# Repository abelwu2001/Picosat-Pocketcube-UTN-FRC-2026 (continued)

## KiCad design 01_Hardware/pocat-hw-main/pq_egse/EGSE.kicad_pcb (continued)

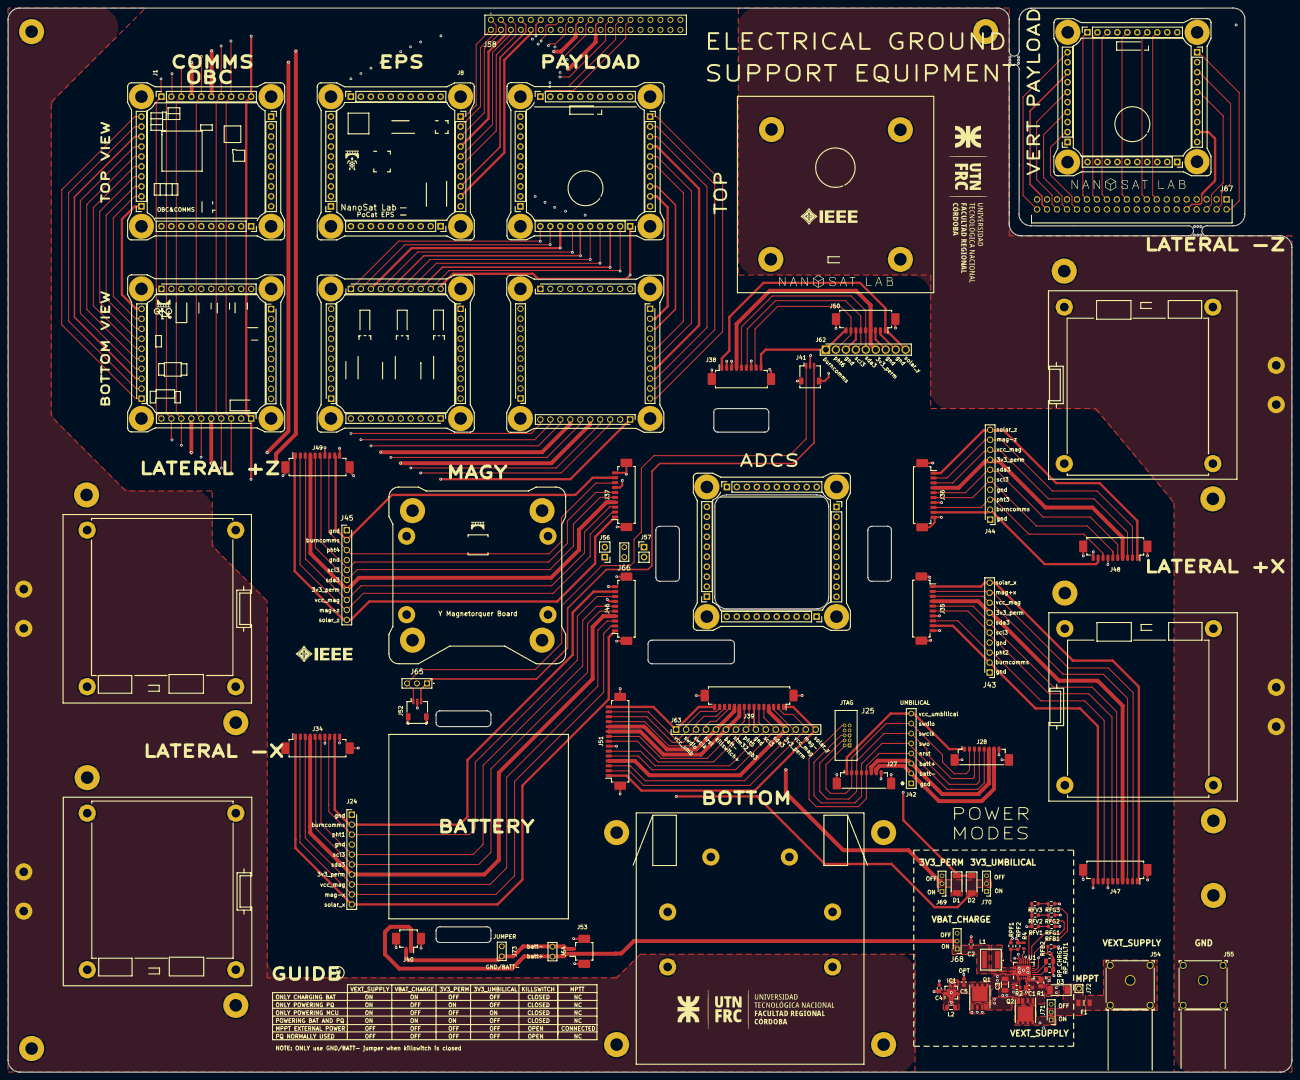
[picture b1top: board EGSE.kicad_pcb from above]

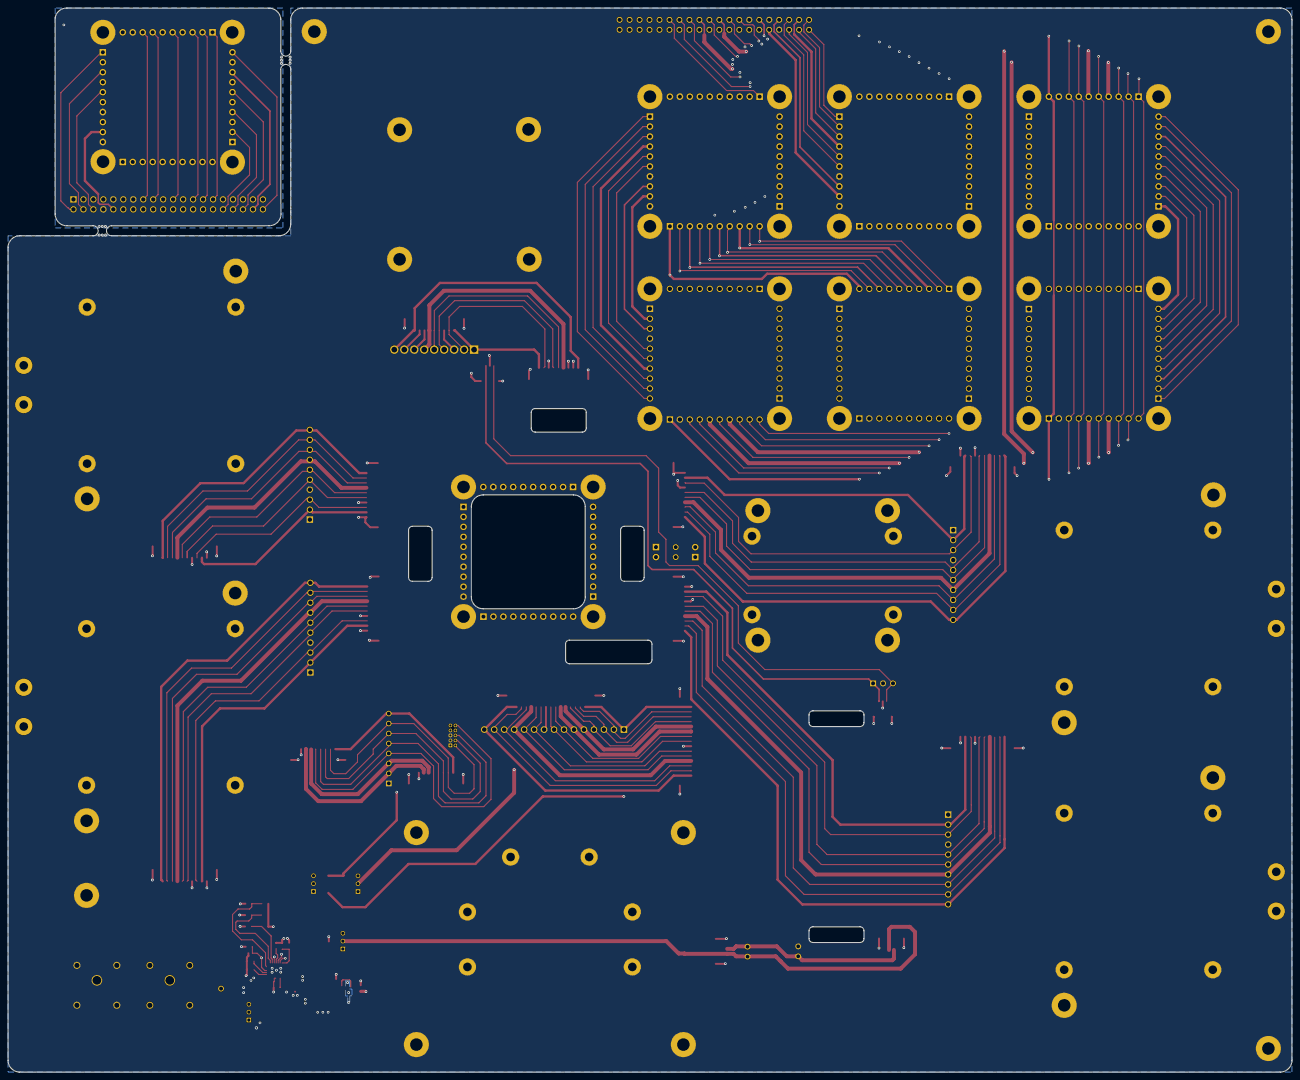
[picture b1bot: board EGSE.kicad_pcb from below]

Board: 6 copper layers, 327.0 x 271.0 mm, 195 parts (2 on the bottom side), 74 nets.

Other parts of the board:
Annotation1#2: Silkscreen_Annotation; IEEE_logo__Annotation1
Annotation1#3, Annotation1#4: Silkscreen_Annotation; Bridgemaker__Annotation1
Annotation2#2: Silkscreen_Annotation; IEEE_logo__Annotation2
Annotation3#2: Silkscreen_Annotation; NSL_long__Annotation3
mouse-bite-2.54mm-slot, mouse-bite-2.54mm-slot#2: VAL**; mouse-bite-2.54mm-slot__mouse-bite-2.54mm-slot

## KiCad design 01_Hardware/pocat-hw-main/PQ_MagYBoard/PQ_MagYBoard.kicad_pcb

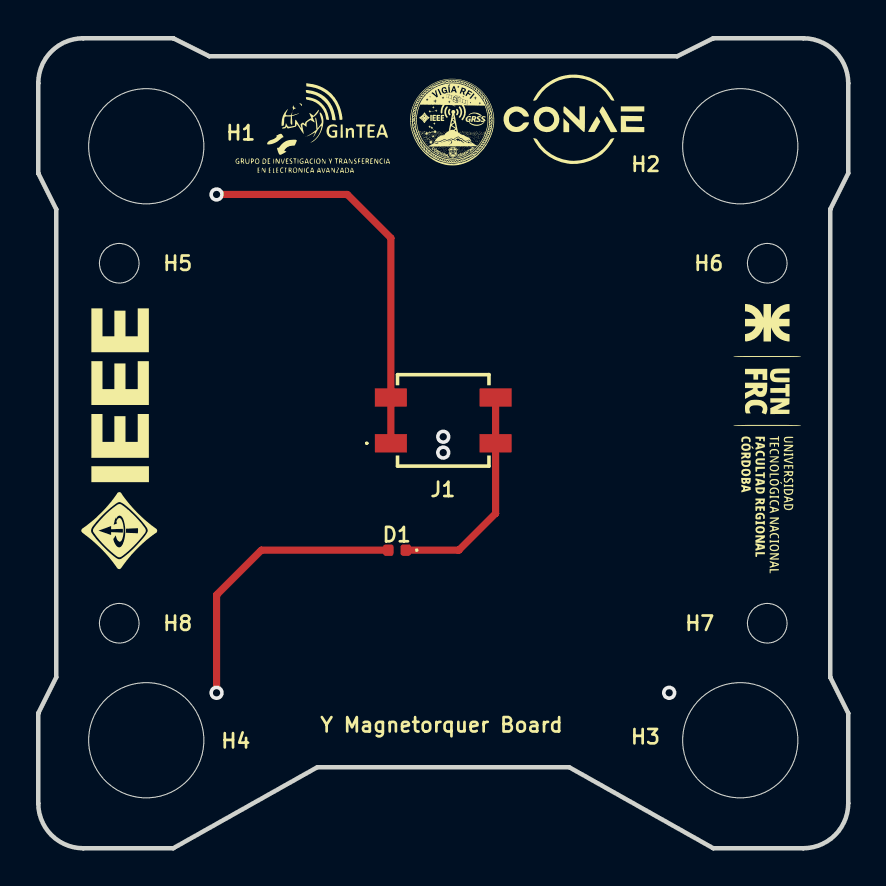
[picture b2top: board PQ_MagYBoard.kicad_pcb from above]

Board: 6 copper layers, 45.0 x 45.0 mm, 11 parts (0 on the bottom side), 2 nets.

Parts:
Annotation1: Silkscreen_Annotation; IEEE_logo__Annotation1
D1: LED; D1__96abf5d7
H1: MountingHole; H1__4e36dd2d
H2: MountingHole; H2__04eba765
H3: MountingHole; H3__b5fb1087
H4: MountingHole; H4__a7a81e5c
H5: MountingHole; H5__5195467b
H6: MountingHole; H6__80f6b20b
H7: MountingHole; H7__513e248b
H8: MountingHole; H8__01ccc00b
J1: M20-7810245; J1__1c8c80f3

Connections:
/MAG+Y: D1.1 (K), J1.2, J1.4
/VCC_MAG: D1.2 (A), J1.1, J1.3

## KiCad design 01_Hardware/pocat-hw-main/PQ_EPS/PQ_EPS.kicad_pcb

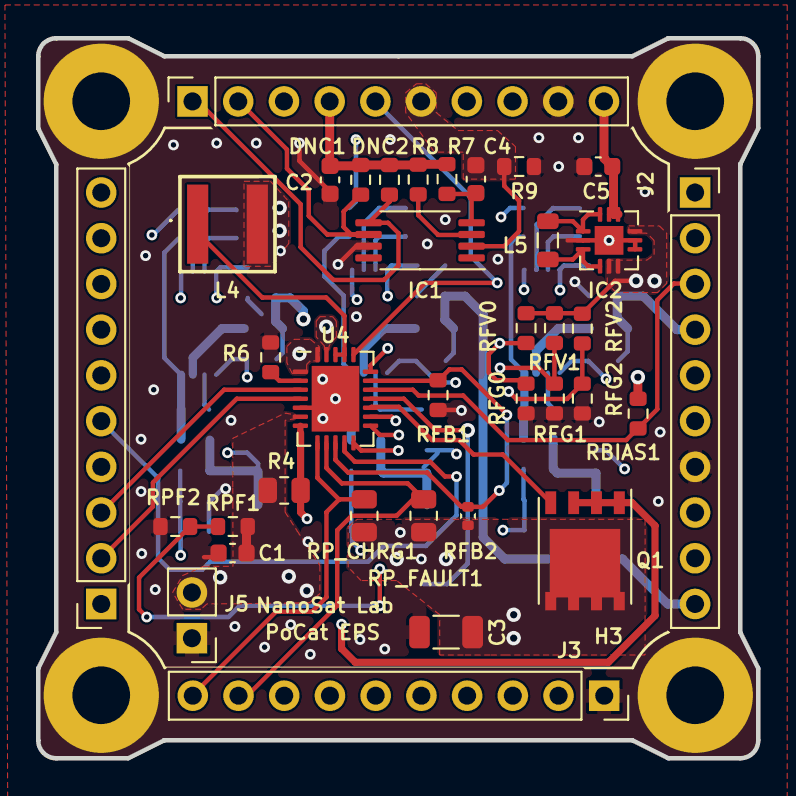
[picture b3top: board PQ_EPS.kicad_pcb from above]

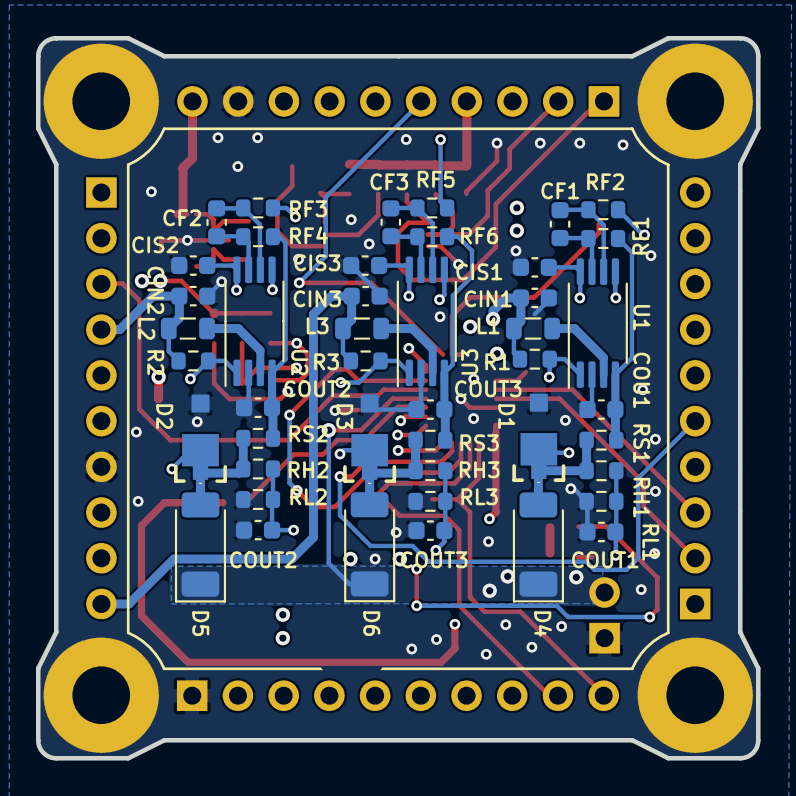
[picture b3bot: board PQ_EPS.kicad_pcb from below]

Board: 4 copper layers, 40.0 x 40.0 mm, 85 parts (45 on the bottom side), 52 nets.

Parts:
C1: 2.2u; C1__85906104
C2: 10u; C2__3bb3261a
C3: 100u; C3__1b16b82f
C4: 0.1u; C4__8813a4fd
C5: 22u; C5__10c63672
CF1: 1u; CF1__1f269640
CF2: 1u; CF2__bf330c01
CF3: 1u; CF3__dc4340d5
CIN1: 1.5u; CIN1__4d5a425d
CIN2: 1.5u; CIN2__61dff1fe
CIN3: 1.5u; CIN3__7a7f343d
CIS1: 1n; CINSNS1__fe801517
CIS2: 1n; CINSNS2__c8bb742b
CIS3: 1n; CINSNS3__0692e306
COU1: 10u; COUT1__ab158bdd
COUT1: 1n; COUTSNS1__a3c0c3c5
COUT2: 10u; COUT2__652cde38
COUT2#2: 1n; COUTSNS2__7fceb7d9
COUT3: 10u; COUT3__754a9436
COUT3#2: 1n; COUTSNS3__d7212c9c
D1: SMM4F; D1__d6a92ff9
D2: SMM4F; D2__ff0ca32b
D3: SMM4F; D3__e18f0f22
D4: shottky; D4__8296a06b
D5: shottky; D5__9ba6cb21
D6: shottky; D6__c3fa03f0
DNC1: 20k; DNC1__f835551e
DNC2: 20k; DNC2__33baa008
H1: MountingHole_Pad; H1__55b0f0f4
H2: MountingHole_Pad; H2__8e44a857
H3: MountingHole_Pad; H3__b7d146b7
H4: MountingHole_Pad; H4__41eeead0
IC1: DS2782E+; IC1__4bc49ce2
IC2: ISL9120IRTNZ; IC2__20e1d699
J1: CES-110-02-L-S; J1__41ef131c
J2: CES-110-02-L-S; J2__a6eda72d
J3: CES-110-02-L-S; J3__f3199705
J4: CES-110-02-L-S; J4__cbe1d312
J5: J5__02e0e550
L1: 10u; L1__28ad8ce4
L2: 10u; L2__ba5a3009
L3: 10u; L3__2d21b16b
L4: 2.2u; L4__0e1a387a
L5: 1u; L5__3c55d55a
Q1: SIR424DP; Q1__7e14e801
R1: 1k; R1__714a8ecb
R2: 1k; R2__9665c163
R3: 1k; R3__0ad47374
R4: 75m; R4__23007612
R6: 2k; R6__9883130c
R7: 510; R7__5afebccb
R8: 1k; R8__c5a4b0be
R9: 15m; R9__b30fbfff
RBIAS1: 10k; RBIAS1__42875ef3
RF1: 1k; RF1__b4a62e9b
RF2: 1k; RF2__79efa971
RF3: 1k; RF3__bcc6cc11
RF4: 1k; RF4__cdcae543
RF5: 1k; RF5__f4b268ee
RF6: 1k; RF6__ccc287bf
RFB1: 68k; RFB1__c3f0ad02
RFB2: 255k; RFB2__4535851b
RFG0: 1k; RFG0__3a5b81d0
RFG1: 1k; RFG1__e70eb10d
RFG2: 1k; RFG2__d57aa5a1
RFV0: 1k; RFV0__0fa13d2d
RFV1: 1k; RFV1__fbfc8f7b
RFV2: 1k; RFV2__f2fc9b41
RH1: 910k; RH1__fc164062
RH2: 910k; RH2__583a5c2e
RH3: 910k; RH3__ecdadcf0
RL1: 360k; RL1__fa346202
RL2: 360k; RL2__b23261de
RL3: 360k; RL3__61c11c4e
RPF1: 147k; RPF1__76985f45
RPF2: 68k; RPF2__25740c8e
RP_CHRG1: 5k; RP_CHRG1__a22c6ae2
RP_FAULT1: 5k; RP_FAULT1__5c0411cb
RS1: 300m; RS1__0808f33b
RS2: 300m; RS2__556b6153
RS3: 300m; RS3__b8c6c485
U1: SPV1040TTR; U1__eb7258e8
U2: SPV1040TTR; U2__41f13721
U3: SPV1040TTR; U3__48f96149
U4: LTC4040IUFD#PBF; U4__55343438

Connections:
3V3_PERM: C5.2, IC2.10 (FB), IC2.11 (VOUT), J1.10, RBIAS1.2
BATT-: C4.2, IC1.2 (VSS), J1.6, R9.1
BATT_NTC: J2.3, RBIAS1.1, U4.17 (NTC)
CHOUT: C3.1, IC2.5 (VIN_1), IC2.6 (VIN_2), IC2.9 (EN), Q1.5 (D), RFB2.2, RFV0.1, RFV1.1, RFV2.1, RP_CHRG1.1, RP_FAULT1.1, U4.1 (VSYS), U4.24 (VSYS)
CHRG: J3.10, RP_CHRG1.2, U4.8 (CHRG#)
CHRGOFF: J4.2, U4.4 (CHGOFF)
CLPROG: J4.3, U4.3 (CLPROG)
F0: RFG0.1, RFV0.2, U4.14 (F0)
F1: RFG1.1, RFV1.2, U4.13 (F1)
F2: RFG2.1, RFV2.2, U4.12 (F2)
FAULT: J3.9, RP_FAULT1.2, U4.9 (FAULT#)
GND: C1.2, C2.2, C3.2, C5.1, CIN1.1, CIN2.1, CIN3.1, CIS1.1, CIS2.1, CIS3.1, COU1.1, COUT1.1, COUT2.1, COUT2#2.1, COUT3.1, COUT3#2.1, D1.2, D2.2, D3.2, H1.1, H2.1, H3.1, H4.1, IC1.7 (SNS), IC2.2 (PGND), IC2.7 (BYPS), IC2.8 (GND), IC2.13 (EP), J1.9, J2.7, J3.1, J5.1, R6.1, R9.2, RFB1.2, RFG0.2, RFG1.2, RFG2.2, RL1.2, RL2.2, RL3.2, RPF2.1, U1.2 (GND), U2.2 (GND), U3.2 (GND), U4.5 (BSTOFF), U4.25 (EPAD)
KILLSWITCH+: C2.1, DNC1.2, DNC2.2, J1.4, L4.2, R7.2, R8.2, U4.23 (BAT)
NRST: J4.5, U4.11 (RST#)
unnamed: D1.1, D4.2, RF2.2, RH1.1, RS1.2
unnamed: D2.1, D5.2, RF3.2, RH2.1, RS2.2
unnamed: D3.1, D6.2, RF5.2, RH3.1, RS3.2
unnamed: C4.1, IC1.4 (VDD), R7.1
unnamed: IC1.3 (VIN), R8.1
unnamed: IC2.3 (LX1_1), IC2.4 (LX1_2), L5.1
unnamed: IC2.1 (LX2_1), IC2.12 (LX2_2), L5.2
unnamed: L4.1, U4.21 (SW), U4.22 (SW)
unnamed: Q1.4 (G), U4.15 (IGATE)
unnamed: CF1.1, RF2.1, U1.6 (ICTRL-MINUS)
unnamed: CF1.2, RF1.1, U1.7 (ICTRL-PLUS)
unnamed: L1.1, U1.3 (LX)
unnamed: CIS1.2, R1.1, U1.1 (MPP-SET), U1.8 (XSHUT)
unnamed: COUT1.2, RH1.2, RL1.1, U1.5 (VCTRL)
unnamed: COU1.2, RF1.2, RS1.1, U1.4 (VOUT)
unnamed: CF2.1, RF3.1, U2.6 (ICTRL-MINUS)
unnamed: CF2.2, RF4.1, U2.7 (ICTRL-PLUS)
unnamed: L2.2, U2.3 (LX)
unnamed: CIS2.2, R2.1, U2.1 (MPP-SET), U2.8 (XSHUT)
unnamed: COUT2#2.2, RH2.2, RL2.1, U2.5 (VCTRL)
unnamed: COUT2.2, RF4.2, RS2.1, U2.4 (VOUT)
unnamed: CF3.1, RF5.1, U3.6 (ICTRL-MINUS)
unnamed: CF3.2, RF6.1, U3.7 (ICTRL-PLUS)
unnamed: L3.2, U3.3 (LX)
unnamed: CIS3.2, R3.1, U3.1 (MPP-SET), U3.8 (XSHUT)
unnamed: COUT3#2.2, RH3.2, RL3.1, U3.5 (VCTRL)
unnamed: COUT3.2, RF6.2, RS3.1, U3.4 (VOUT)
unnamed: RFB1.1, RFB2.1, U4.10 (RSTFB), U4.18 (BSTFB)
unnamed: Q1.1 (S), Q1.2 (S), Q1.3 (S), R4.2, U4.7 (CLN)
unnamed: RPF1.1, RPF2.2, U4.19 (PFI)
OVSNS: C1.1, D4.1, D5.1, D6.1, J5.2, R4.1, RPF1.2, U4.6 (VIN), U4.16 (OVSNS)
PFO: J1.5, U4.20 (PF0#)
PROG: R6.2, U4.2 (PROG)
SCL1: DNC1.1, IC1.6 (SCL), J1.2
SDA1: DNC2.1, IC1.5 (SDA), J1.1
SOLAR_X: CIN1.2, J4.1, L1.2, R1.2
SOLAR_Y: CIN2.2, J2.4, L2.1, R2.2
SOLAR_Z: CIN3.2, J2.10, L3.1, R3.2

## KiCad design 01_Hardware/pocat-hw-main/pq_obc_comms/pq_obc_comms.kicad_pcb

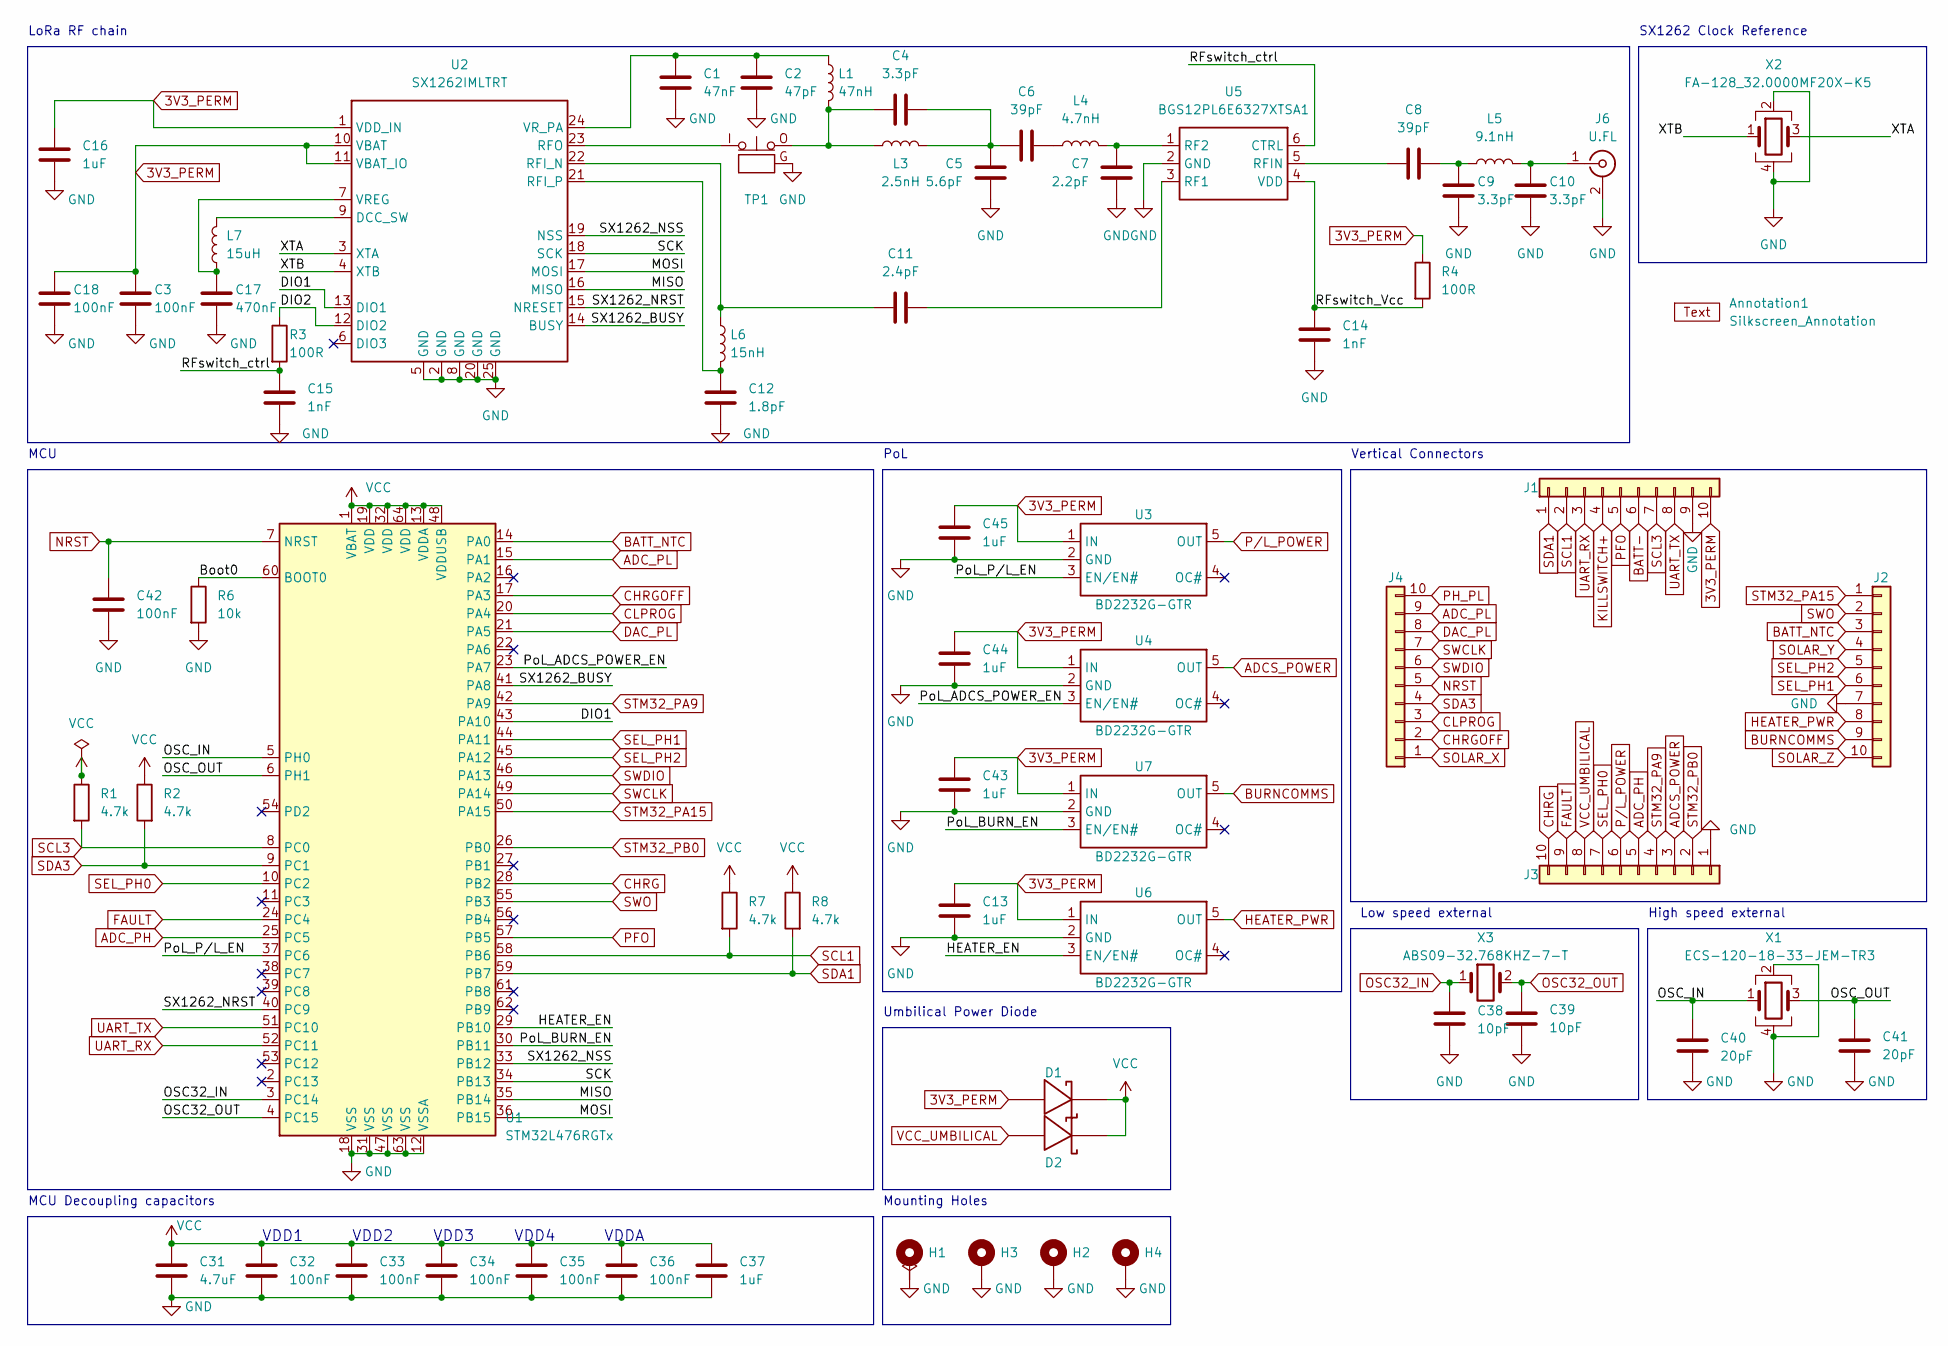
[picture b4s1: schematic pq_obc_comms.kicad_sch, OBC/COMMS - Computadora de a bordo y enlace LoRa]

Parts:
Annotation1: Silkscreen_Annotation; Annotation1__e7e7156d
C1: 47nF; C1__ca774a57; Manufacturer Part Numbe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 GRM155R71C473KA01J
C2: 47pF; C2__72c49c38; Manufacturer Part Numbe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 GJM1555C1H470JB01J
C3: 100nF; C3__bcfd69c3; Manufacturer Part Numbe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 GRM188R72A104KA35J
C4: 3.3pF; C4__90207b2c; Manufacturer Part Numbe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 600L3R3BT200T
C5: 5.6pF; C5__346fd701; Manufacturer Part Numbe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 600L5R6BTN200T
C6: 39pF; C6__2c3003df; Manufacturer Part Numbe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 GJM1555C1H390FB01D
C7: 2.2pF; C7__ead5be2a; Manufacturer Part Numbe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 600L2R2BT200T
C8: 39pF; C8__3b28bfd6; Manufacturer Part Numbe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 GJM1555C1H390FB01D
C9: 3.3pF; C9__dc49ac9c; Manufacturer Part Numbe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 600L3R3BT200T
C10: 3.3pF; C10__82ed297d; Manufacturer Part Numbe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 600L3R3BT200T
C11: 2.4pF; C11__b2db7fb1; Manufacturer Part Numbe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 600L2R4BW200T
C12: 1.8pF; C12__b2c7e8c6; Manufacturer Part Numbe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 600L1R8BW200T
C13: 1uF; C13__d1b90dea; Manufacturer Part Numbe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 GRM188R61A105KA61D
C14: 1nF; C14__c8ce7f45; Manufacturer Part Numbe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 0603B102K500CT
C15: 1nF; C15__0dffcb91; Manufacturer Part Numbe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 0603B102K500CT
C16: 1uF; C16__58b6b3e1; Manufacturer Part Numbe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 GRM188R61A105KA61D
C17: 470nF; C17__74bd322c; Manufacturer Part Numbe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 GRM188R7YA474KE05D
C18: 100nF; C18__0129d3c2; Manufacturer Part Numbe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 GRM188R72A104KA35J
C31: 4.7uF; C31__e4047c3f; Manufacturer Part Numbe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 GRT188R61E475KE13D
C32: 100nF; C32__096e5967; Manufacturer Part Numbe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 GRM188R72A104KA35J
C33: 100nF; C33__1d37b461; Manufacturer Part Numbe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 GRM188R72A104KA35J
C34: 100nF; C34__f54a60c3; Manufacturer Part Numbe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 GRM188R72A104KA35J
C35: 100nF; C35__eea0baec; Manufacturer Part Numbe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 GRM188R72A104KA35J
C36: 100nF; C36__1330f687; Manufacturer Part Numbe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 GRM188R72A104KA35J
C37: 1uF; C37__f9cb8991; Manufacturer Part Numbe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 GRM188R61A105KA61D
C38: 10pF; C38__fabc3299; Manufacturer Part Numbe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 06035A100GAT2A
C39: 10pF; C39__0234df5a; Manufacturer Part Numbe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 06035A100GAT2A
C40: 20pF; C40__9df9f696; Manufacturer Part Numbe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 GCM1885C2A200JA16D
C41: 20pF; C41__0aea1b69; Manufacturer Part Numbe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 GCM1885C2A200JA16D
C42: 100nF; C42__d2aef4f4; Manufacturer Part Numbe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 GRM188R72A104KA35J
C43: 1uF; C43__5c5681ac; Manufacturer Part Numbe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 GRM188R61A105KA61D
C44: 1uF; C44__a1850039; Manufacturer Part Numbe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 GRM188R61A105KA61D
C45: 1uF; C45__bee54487; Manufacturer Part Numbe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 GRM188R61A105KA61D
D1: RBS1LAM40ATR; D1__334df4c5; Manufacturer Part Numbe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 RBS1LAM40ATR
D2: RBS1LAM40ATR; D2__bd2b3331; Manufacturer Part Numbe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 RBS1LAM40ATR
H1: MountingHole_Pad; H1__a8eef03d
H2: MountingHole_Pad; H2__7afaf494
H3: MountingHole_Pad; H3__f70388f1
H4: MountingHole_Pad; H4__f801a1cd
J1: Conn_01x10; J1__ce21188f; Manufacturer Part Numbe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 CES-110-01-T-S
J2: Conn_01x10; J2__a63bc9cd; Manufacturer Part Numbe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 CES-110-01-T-S
J3: Conn_01x10; J3__57c77339; Manufacturer Part Numbe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 CES-110-01-T-S
J4: Conn_01x10; J4__71042816; Manufacturer Part Numbe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 CES-110-01-T-S
J6: U.FL; J6__95db4f5f; Manufacturer Part Numbe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 U.FL-R-SMT-1(10)
L1: 47nH; L1__f2e2799c; Manufacturer Part Numbe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 0402DC-47NXGRW
L3: 2.5nH; L3__1485d6de; Manufacturer Part Numbe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 LQW15AN2N5B00D
L4: 4.7nH; L4__942f3cf4; Manufacturer Part Numbe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 0402DC-4N7XGRW
L5: 9.1nH; L5__47193893; Manufacturer Part Numbe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 LQW15AN9N1G8ZD
L6: 15nH; L6__ced7a93c; Manufacturer Part Numbe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 LQW15AN15NH00D
L7: 15uH; L7__e08a8504; Manufacturer Part Numbe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 LQM21DN150M70L
R1: 4.7k; R1__fba2bbee; Manufacturer Part Numbe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 CRCW06034K70JNEAC
R2: 4.7k; R2__b8740f1f; Manufacturer Part Numbe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 CRCW06034K70JNEAC
R3: 100R; R3__a8354450; Manufacturer Part Numbe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 RC0603JR-07100RL
R4: 100R; R4__2f764c92; Manufacturer Part Numbe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 RC0603JR-07100RL
R6: 10k; R6__0c1c77f0; Manufacturer Part Numbe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 CRCW040220K0FKEDC
R7: 4.7k; R7__ea538916; Manufacturer Part Numbe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 CRCW06034K70JNEAC
R8: 4.7k; R8__1b786c22; Manufacturer Part Numbe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 CRCW06034K70JNEAC
TP1: CoaxialSwitch_Testpoint; TP1__f9c4e3d2; Manufacturer Part Numbe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 MS-156C3(20)
U1: STM32L476RGTx; U1__2d765caa; Manufacturer Part Numbe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 STM32L476RGT6
U2: SX1262IMLTRT; U2__3c01bf78; Manufacturer Part Numbe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 SX1262IMLTRT
U3: BD2232G-GTR; U3__78de66fb; Manufacturer Part Numbe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 BD2232G-GTR
U4: BD2232G-GTR; U4__5f493963; Manufacturer Part Numbe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 BD2232G-GTR
U5: BGS12PL6E6327XTSA1; U5__751f0fcc; Manufacturer Part Numbe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 BGS12PL6E6327XTSA1
U6: BD2232G-GTR; U6__e26a39a5; Manufacturer Part Numbe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 BD2232G-GTR
U7: BD2232G-GTR; U7__1728c99a; Manufacturer Part Numbe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 BD2232G-GTR
X1: ECS-120-18-33-JEM-TR3; X1__85b5baba; Manufacturer Part Numbe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 ECS-120-18-33-JEM-TR3
X2: FA-128_32.0000MF20X-K5; X2__c5377c9d; Manufacturer Part Numbe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 FA-128 32.0000MF20X-K5
X3: ABS09-32.768KHZ-7-T; X3__40ef0054; Manufacturer Part Numbe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 ABS09-32.768KHZ-7-T

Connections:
3V3_PERM: C3.1, C13.1, C16.1, C18.1, C43.1, C44.1, C45.2, D1.2, J1.10, R4.1, U2.1 (VDD_IN), U2.10 (VBAT), U2.11 (VBAT_IO), U3.1 (IN), U4.1 (IN), U6.1 (IN), U7.1 (IN)
/Boot0: R6.1, U1.60 (BOOT0)
/DIO1: U1.43 (PA10), U2.13 (DIO1)
/DIO2: R3.1, U2.12 (DIO2)
/HEATER_EN: U1.29 (PB10), U6.3 (EN/EN#)
/MISO: U1.35 (PB14), U2.16 (MISO)
/MOSI: U1.36 (PB15), U2.17 (MOSI)
/OSC_IN: C40.1, U1.5 (PH0), X1.1
/OSC_OUT: C41.1, U1.6 (PH1), X1.3
/PoL_ADCS_POWER_EN: U1.23 (PA7), U4.3 (EN/EN#)
/PoL_BURN_EN: U1.30 (PB11), U7.3 (EN/EN#)
/PoL_P/L_EN: U1.37 (PC6), U3.3 (EN/EN#)
/RFswitch_Vcc: C14.1, R4.2, U5.4 (VDD)
/RFswitch_ctrl: C15.1, R3.2, U5.6 (CTRL)
/SCK: U1.34 (PB13), U2.18 (SCK)
/SX1262_BUSY: U1.41 (PA8), U2.14 (BUSY)
/SX1262_NRST: U1.40 (PC9), U2.15 (NRESET)
/SX1262_NSS: U1.33 (PB12), U2.19 (NSS)
/XTA: U2.3 (XTA), X2.3
/XTB: U2.4 (XTB), X2.1
ADCS_POWER: J3.3, U4.5 (OUT)
ADC_PH: J3.5, U1.25 (PC5)
ADC_PL: J4.9, U1.15 (PA1)
BATT-: J1.6
BATT_NTC: J2.3, U1.14 (PA0)
BURNCOMMS: J2.9, U7.5 (OUT)
CHRG: J3.10, U1.28 (PB2)
CHRGOFF: J4.2, U1.17 (PA3)
CLPROG: J4.3, U1.20 (PA4)
DAC_PL: J4.8, U1.21 (PA5)
FAULT: J3.9, U1.24 (PC4)
GND: C1.2, C2.2, C3.2, C5.2, C7.2, C9.2, C10.2, C12.2, C13.2, C14.2, C15.2, C16.2, C17.2, C18.2, C31.2, C32.2, C33.2, C34.2, C35.2, C36.2, C37.2, C38.2, C39.2, C40.2, C41.2, C42.2, C43.2, C44.2, C45.1, H1.1, H2.1, H3.1, H4.1, J1.9, J2.7, J3.1, J6.2 (Ext), R6.2, TP1.G, U1.12 (VSSA), U1.18 (VSS), U1.31 (VSS), U1.47 (VSS), U1.63 (VSS), U2.2 (GND), U2.5 (GND), U2.8 (GND), U2.20 (GND), U2.25 (GND), U3.2 (GND), U4.2 (GND), U5.2 (GND), U6.2 (GND), U7.2 (GND), X1.2, X1.4, X2.2, X2.4
HEATER_PWR: J2.8, U6.5 (OUT)
KILLSWITCH+: J1.4
NRST: C42.1, J4.5, U1.7 (NRST)
unnamed: C4.1, L1.2, L3.1, TP1.O
unnamed: C4.2, C5.1, C6.1, L3.2
unnamed: C6.2, L4.1
unnamed: C8.2, C9.1, L5.1
unnamed: C10.1, J6.1 (In), L5.2
unnamed: L7.2, U2.9 (DCC_SW)
unnamed: C11.1, L6.1, U2.22 (RFI_N)
unnamed: C12.1, L6.2, U2.21 (RFI_P)
unnamed: TP1.I, U2.23 (RFO)
unnamed: C17.1, L7.1, U2.7 (VREG)
unnamed: C1.1, C2.1, L1.1, U2.24 (VR_PA)
unnamed: C11.2, U5.3 (RF1)
unnamed: C7.1, L4.2, U5.1 (RF2)
unnamed: C8.1, U5.5 (RFIN)
OSC32_IN: C38.1, U1.3 (PC14), X3.1
OSC32_OUT: C39.1, U1.4 (PC15), X3.2
PFO: J1.5, U1.57 (PB5)
PH_PL: J4.10
SCL1: J1.2, R7.2, U1.58 (PB6)
SCL3: J1.7, R1.2, U1.8 (PC0)
SDA1: J1.1, R8.2, U1.59 (PB7)
SDA3: J4.4, R2.2, U1.9 (PC1)
SEL_PH0: J3.7, U1.10 (PC2)
SEL_PH1: J2.6, U1.44 (PA11)
SEL_PH2: J2.5, U1.45 (PA12)
SOLAR_X: J4.1
SOLAR_Y: J2.4
SOLAR_Z: J2.10
STM32_PA9: J3.4, U1.42 (PA9)
STM32_PA15: J2.1, U1.50 (PA15)
STM32_PB0: J3.2, U1.26 (PB0)
SWCLK: J4.7, U1.49 (PA14)
SWDIO: J4.6, U1.46 (PA13)
SWO: J2.2, U1.55 (PB3)
UART_RX: J1.3, U1.52 (PC11)
UART_TX: J1.8, U1.51 (PC10)
VCC: C31.1, C32.1, C33.1, C34.1, C35.1, C36.1, C37.1, D1.1, D2.1, R1.1, R2.1, R7.1, R8.1, U1.1 (VBAT), U1.13 (VDDA), U1.19 (VDD), U1.32 (VDD), U1.48 (VDDUSB), U1.64 (VDD)
VCC_UMBILICAL: D2.2, J3.8

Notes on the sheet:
VDD2
MCU Decoupling capacitors
LoRa RF chain
SX1262 Clock Reference
Umbilical Power Diode
VDD1
Low speed external
Vertical Connectors
MCU
VDD3
VDDA
High speed external
Mounting Holes
VDD4
PoL

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
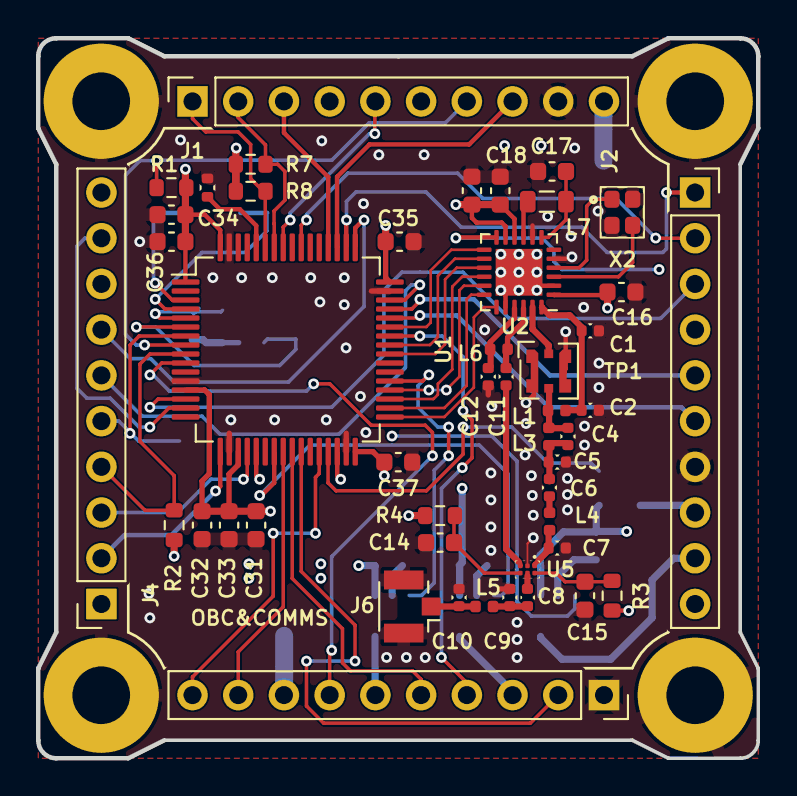
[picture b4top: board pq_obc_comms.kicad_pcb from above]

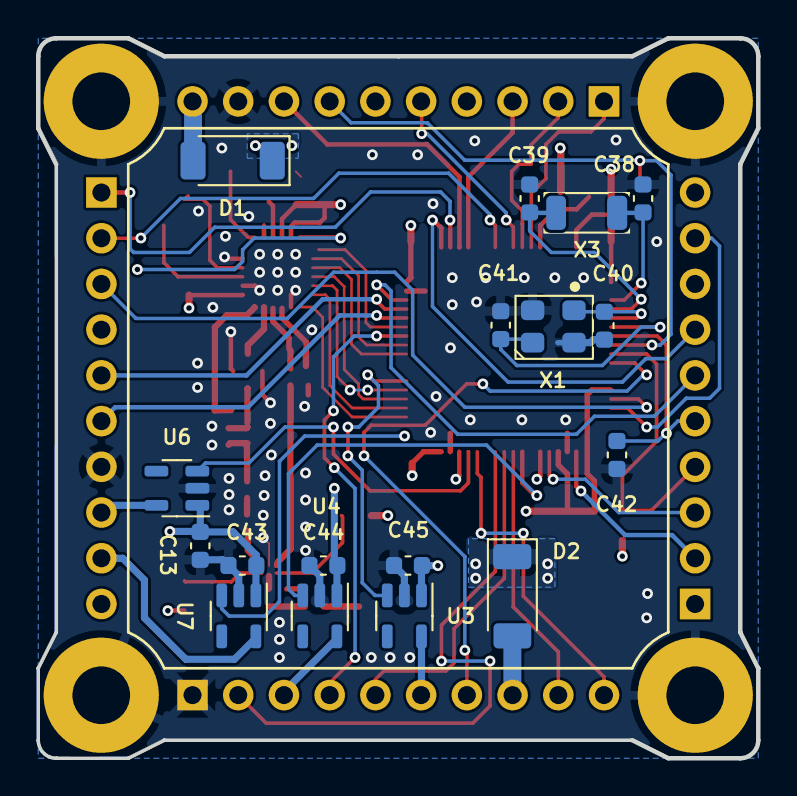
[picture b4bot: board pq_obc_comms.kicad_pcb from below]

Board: 4 copper layers, 40.0 x 40.0 mm, 68 parts (17 on the bottom side), 68 nets.

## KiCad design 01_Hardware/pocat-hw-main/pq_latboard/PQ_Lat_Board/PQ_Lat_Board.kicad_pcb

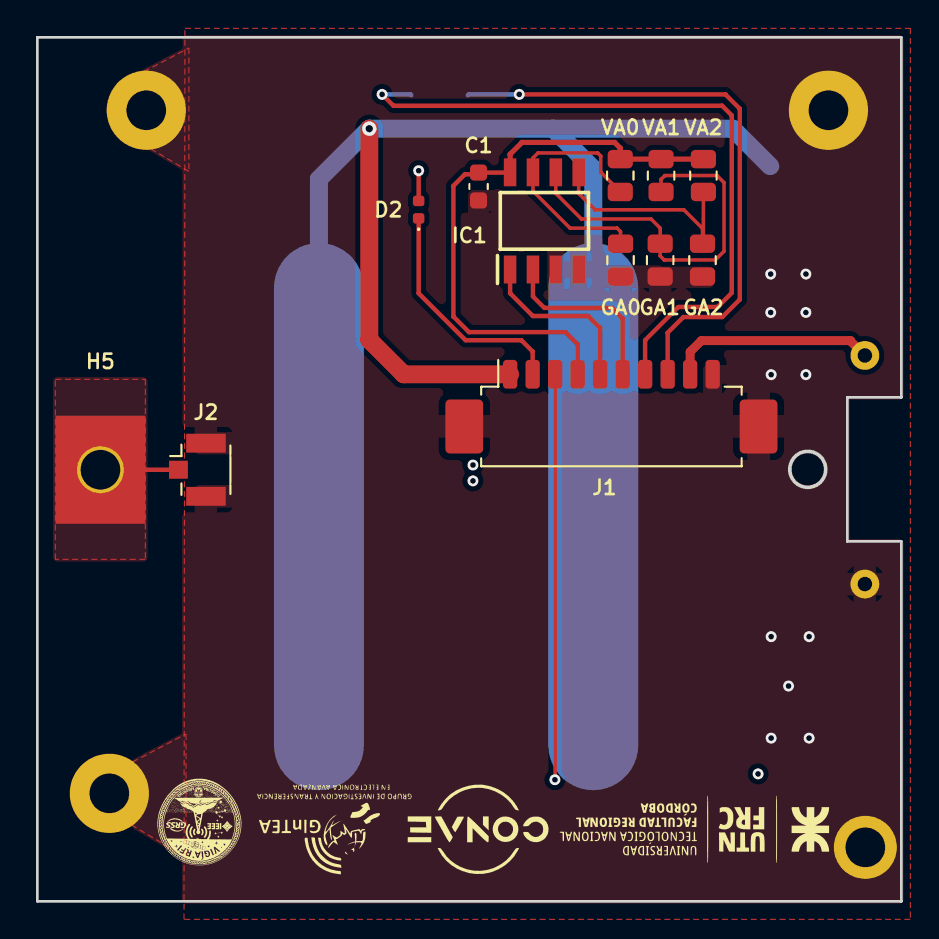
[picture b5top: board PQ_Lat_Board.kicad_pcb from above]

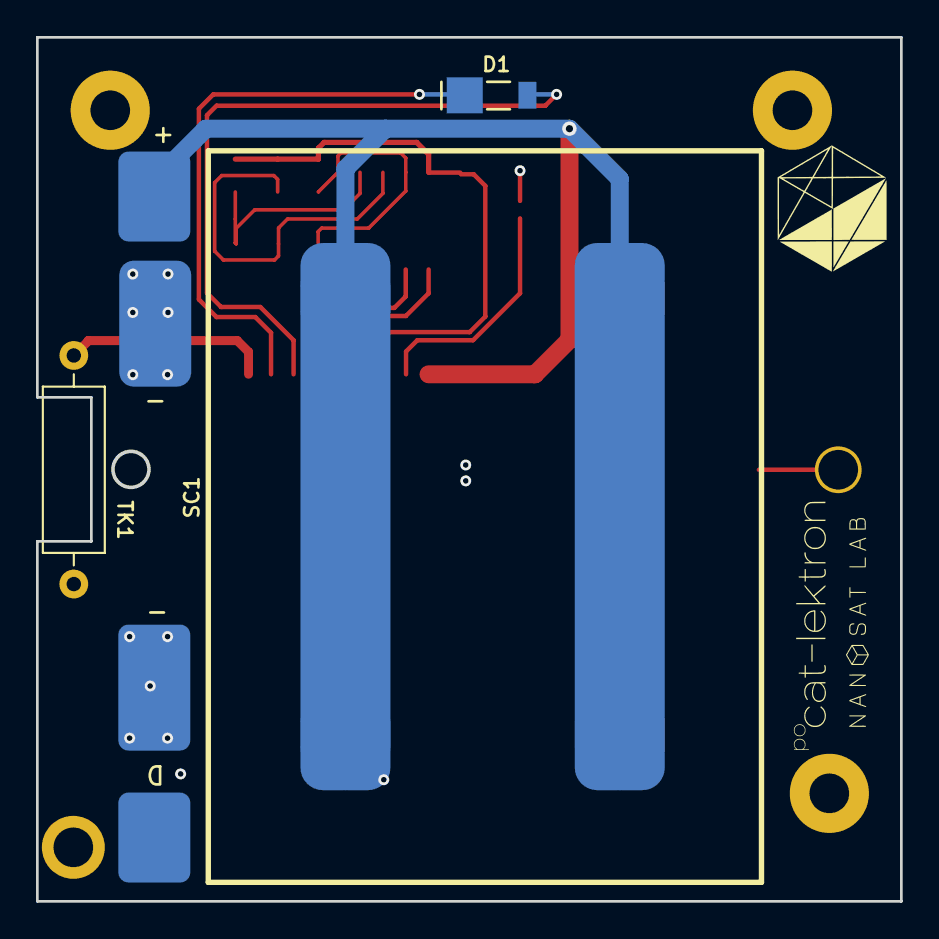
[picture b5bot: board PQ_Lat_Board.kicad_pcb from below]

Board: 6 copper layers, 48.0 x 48.0 mm, 22 parts (6 on the bottom side), 14 nets.

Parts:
Annotation3: pocat-lektron; pocat_lektron
Annotation4: Logo lektron; NSL_hexagon
Annotation6: Nanosatlab; NSL-small
C1: 1 uF; C_0603_1608Metric
D1: SLCD-61N8
D2: LED; LED_0402_1005Metric
GA0, GA1, GA2: 0R; R_0805_2012Metric
H1, H2, H3, H4: MountingHole_Pad; MountingHole_2.2mm_M2_Pad
H5: MountingHole_Pad; MountingHole_2.2mm_M2_DIN965_Pad_TopOnly
IC1: TCN75AVOA713; TCN75AVOA
J1: Conn_01x11_MountingPin; Molex_PicoBlade_53261-1071_1x10-1MP_P1.25mm_Horizontal
J2: Conn_Coaxial; U.FL_Hirose_U.FL-R-SMT-1_Vertical
SC1: Lighttricity_S3040_CIC
TK1: 4.7; R_Axial_DIN0309_L9.0mm_D3.2mm_P12.70mm_Horizontal
VA0, VA1, VA2: 0R; R_0805_2012Metric

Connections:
/ADCS: D2.1 (K), J1.2
/Antenna Connector: H5.1, J2.1 (In)
/BURNCOMMS: J1.9, TK1.1
/PH+: D1.2, J1.8
/PH-: D1.1, J1.7
/SCL: IC1.2 (SCL), J1.6
/SDA: IC1.1 (SDA), J1.5
/SOLAR: J1.1, SC1.3
/VCC: C1.1, IC1.8 (VDD), J1.4, VA0.2, VA1.2, VA2.2
/VCC_MAG: D2.2 (A), J1.3
GND: C1.2, GA0.2, GA1.2, GA2.2, H1.1, H2.1, H3.1, H4.1, IC1.3 (ALERT), IC1.4 (GND), J1.10, J1.MP (MountPin), J2.2 (Ext), SC1.1, TK1.2
unnamed: GA0.1, IC1.7 (A0), VA0.1
unnamed: GA1.1, IC1.6 (A1), VA1.1
unnamed: GA2.1, IC1.5 (A2), VA2.1
